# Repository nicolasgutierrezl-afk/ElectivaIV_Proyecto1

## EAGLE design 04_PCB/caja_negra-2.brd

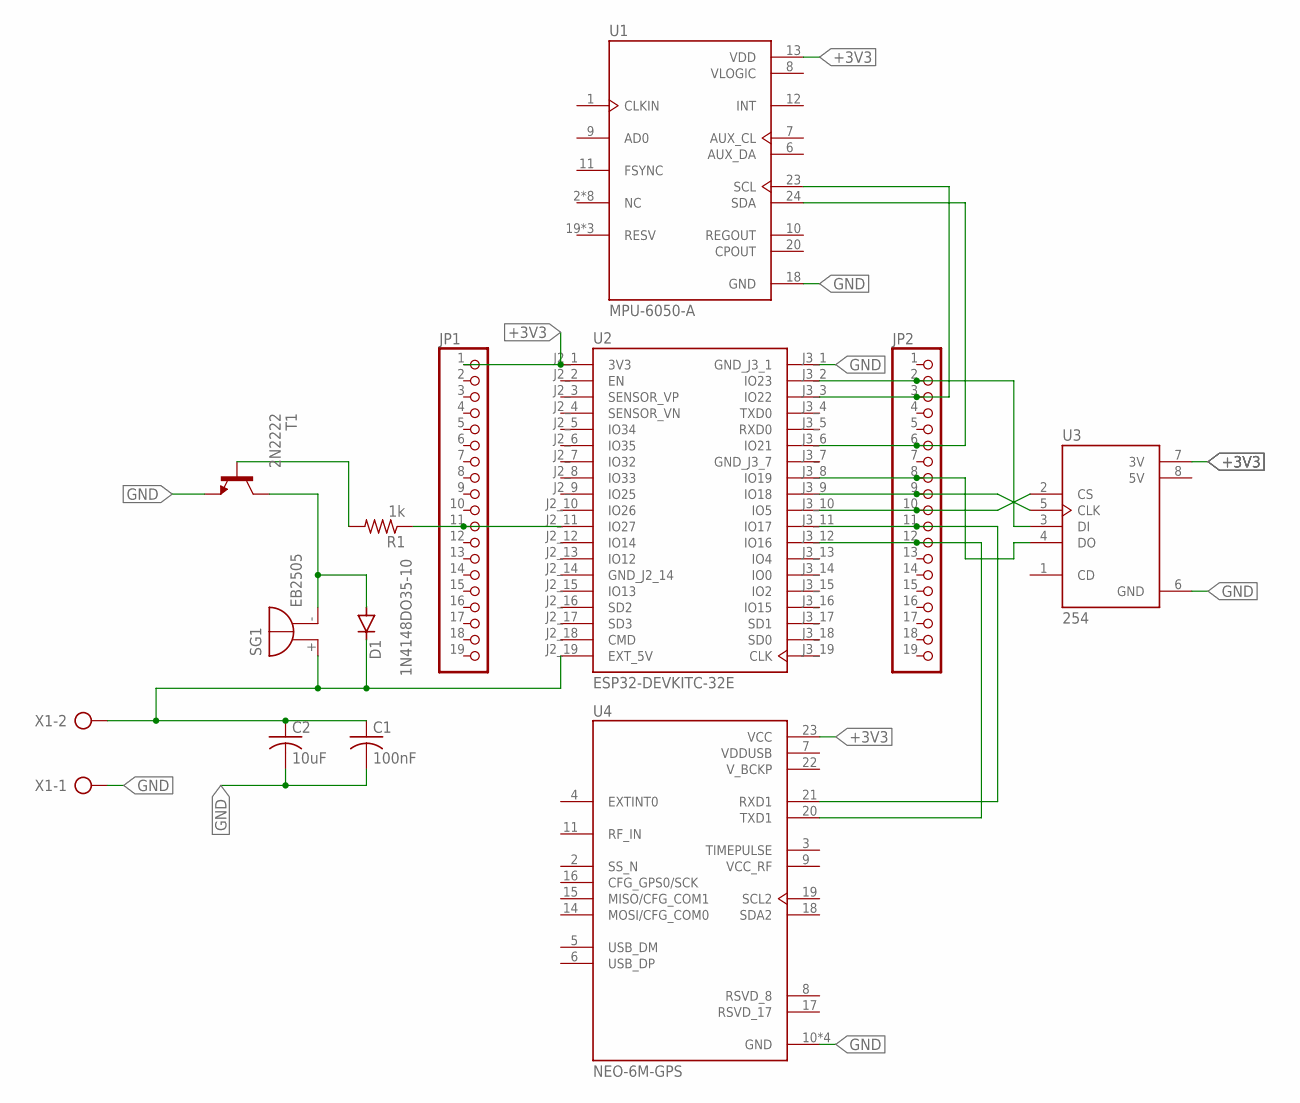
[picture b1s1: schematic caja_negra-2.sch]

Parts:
C1: 100nF; C025-024X044
C2: 10uF; C025-024X044
D1: 1N4148DO35-10; DO35-10
JP1, JP2: PINHD-1X19; 1X19
R1: 1k; 0204V
SG1: EB2505
T1: 2N2222; TO18
U1: MPU-6050-A; QFN50P400X400X95-24N
U2: ESP32-DEVKITC-32E; MODULE_ESP32-DEVKITC-32E
U3: 254; MODULE_254
U4: NEO-6M-GPS; XCVR_NEO-6M-GPS
X1: AK500/2-H

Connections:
5V: U3.8 (5V)
+3V3: JP1.1, U1.13 (VDD), U2.J2_1 (3V3), U3.7 (3V), U4.23 (VCC)
GND: C1.2, C2.2, T1.1 (E), U1.18 (GND), U2.J3_1 (GND_J3_1), U3.6 (GND), U4.10 (GND), U4.12 (GND), U4.13 (GND), U4.24 (GND), X1.1
GND_J2_14: U2.J2_14 (GND_J2_14)
GND_J3_7: U2.J3_7 (GND_J3_7)
unnamed: JP2.6, U1.24 (SDA), U2.J3_6 (IO21)
unnamed: JP2.3, U1.23 (SCL), U2.J3_3 (IO22)
unnamed: JP2.12, U2.J3_12 (IO16), U4.20 (TXD1)
unnamed: JP2.11, U2.J3_11 (IO17), U4.21 (RXD1)
unnamed: JP2.2, U2.J3_2 (IO23), U3.3 (DI)
unnamed: JP2.10, U2.J3_10 (IO5), U3.2 (CS)
unnamed: JP2.9, U2.J3_9 (IO18), U3.5 (CLK)
unnamed: JP2.8, U2.J3_8 (IO19), U3.4 (DO)
unnamed: JP1.11, R1.1, U2.J2_11 (IO27)
unnamed: C1.1, C2.1, D1.C, SG1.+, U2.J2_19 (EXT_5V), X1.2
unnamed: D1.A, SG1.-, T1.3 (C)
unnamed: R1.2, T1.2 (B)
VDDUSB: U4.7 (VDDUSB)
VLOGIC: U1.8 (VLOGIC)
V_BCKP: U4.22 (V_BCKP)

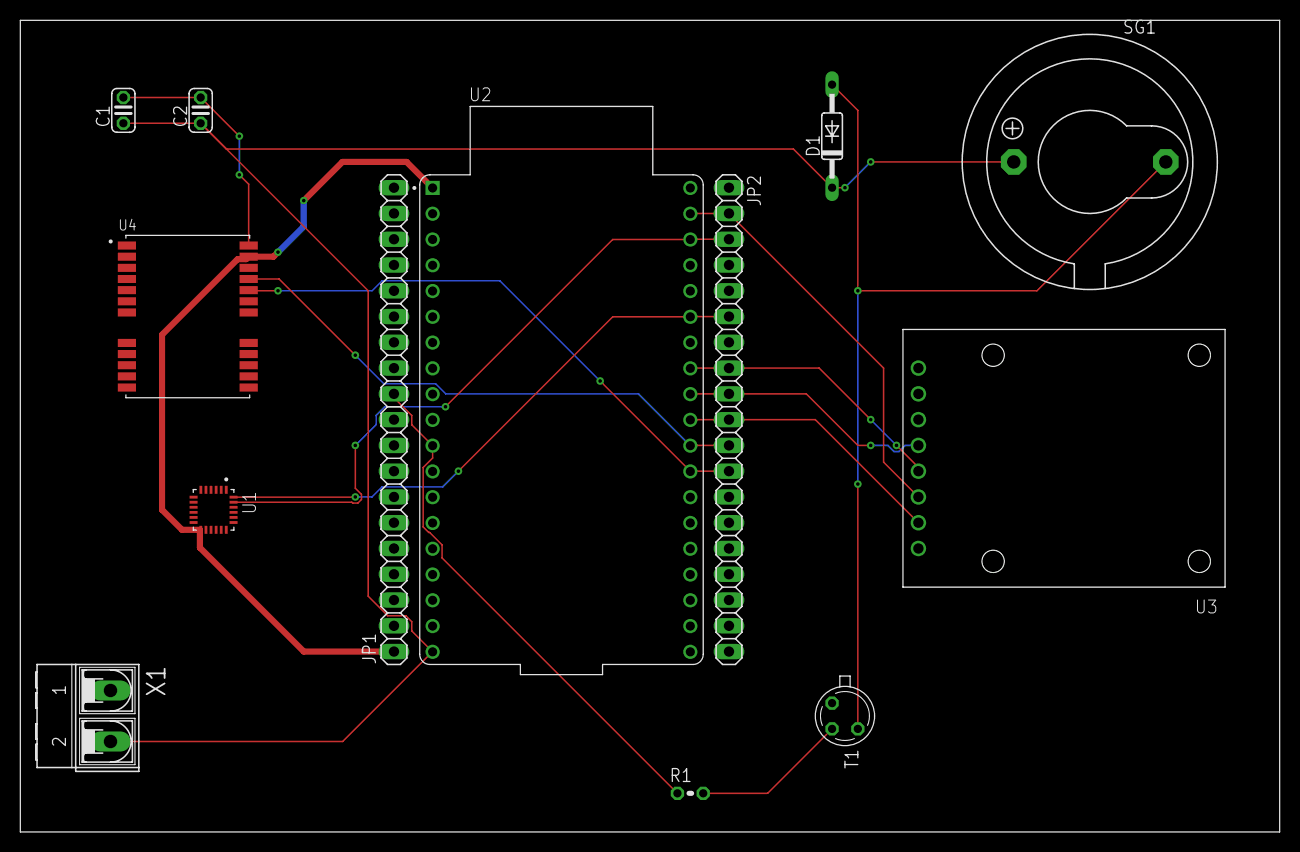
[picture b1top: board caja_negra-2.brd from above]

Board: 2 copper layers, 124.1 x 80.0 mm, 13 parts (0 on the bottom side), 14 nets.

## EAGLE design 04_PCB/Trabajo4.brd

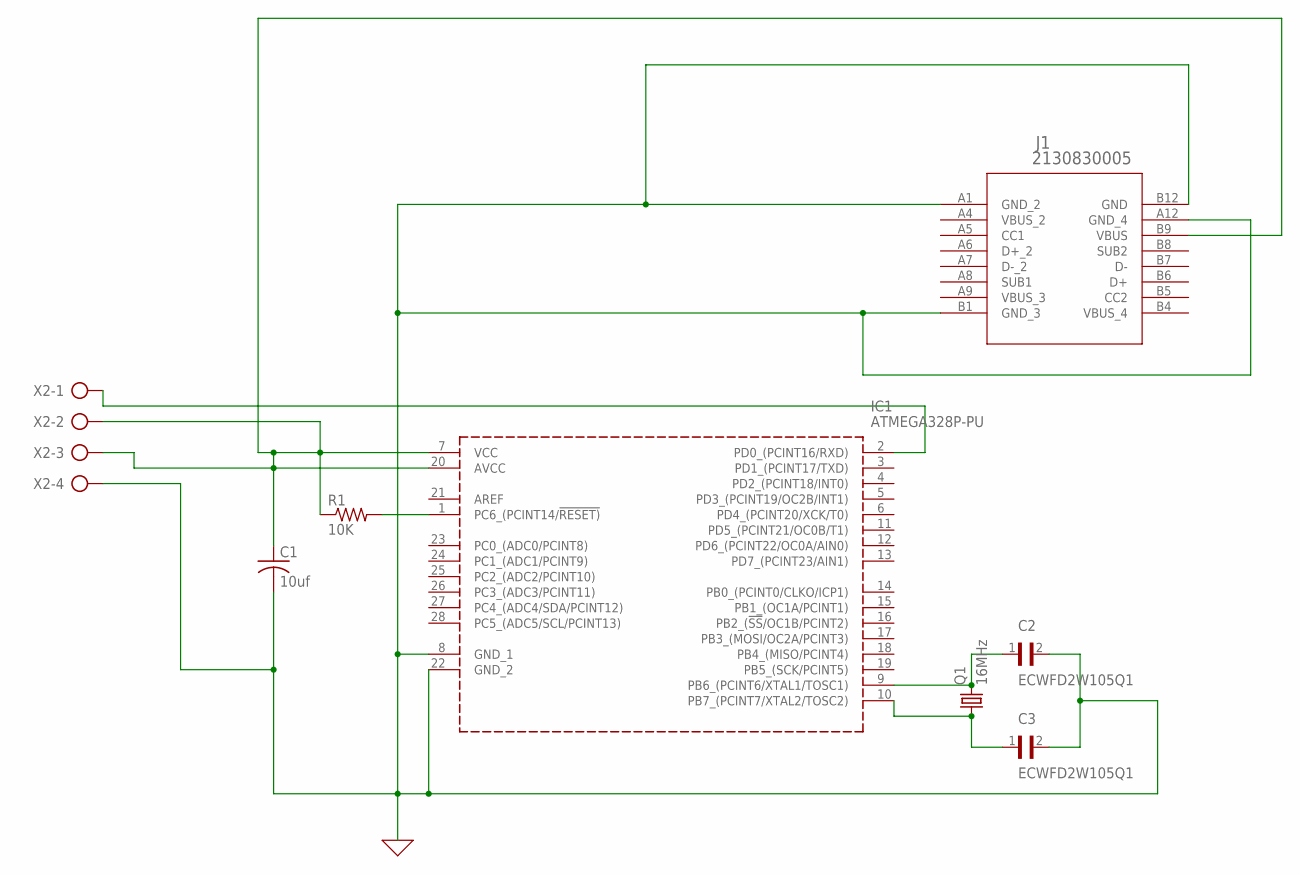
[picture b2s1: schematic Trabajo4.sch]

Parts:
C1: 10uf; C025-024X044
C2, C3: ECWFD2W105Q1; CAPRR1000W60L1260T920H1390
IC1: ATMEGA328P-PU; DIP794W53P254L3467H457Q28N
J1: 2130830005; 2130830005_MOL
Q1: 16MHz; HC33U-V
R1: 10K; 0204V
X2: AK500/4-H

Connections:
0: C1.2, C2.2, C3.2, IC1.8 (GND_1), IC1.22 (GND_2), J1.A1 (GND_2), J1.A12 (GND_4), J1.B1 (GND_3), J1.B12 (GND), X2.4
unnamed: C2.1, IC1.9 (PB6_(PCINT6/XTAL1/TOSC1)), Q1.2
unnamed: C3.1, IC1.10 (PB7_(PCINT7/XTAL2/TOSC2)), Q1.1
unnamed: IC1.2 (PD0_(PCINT16/RXD)), X2.1
unnamed: IC1.1 (PC6_(PCINT14/!RESET)), R1.2
unnamed: C1.1, IC1.7 (VCC), IC1.20 (AVCC), J1.B9 (VBUS), R1.1, X2.2, X2.3
VBUS_2: J1.A4 (VBUS_2)
VBUS_3: J1.A9 (VBUS_3)
VBUS_4: J1.B4 (VBUS_4)

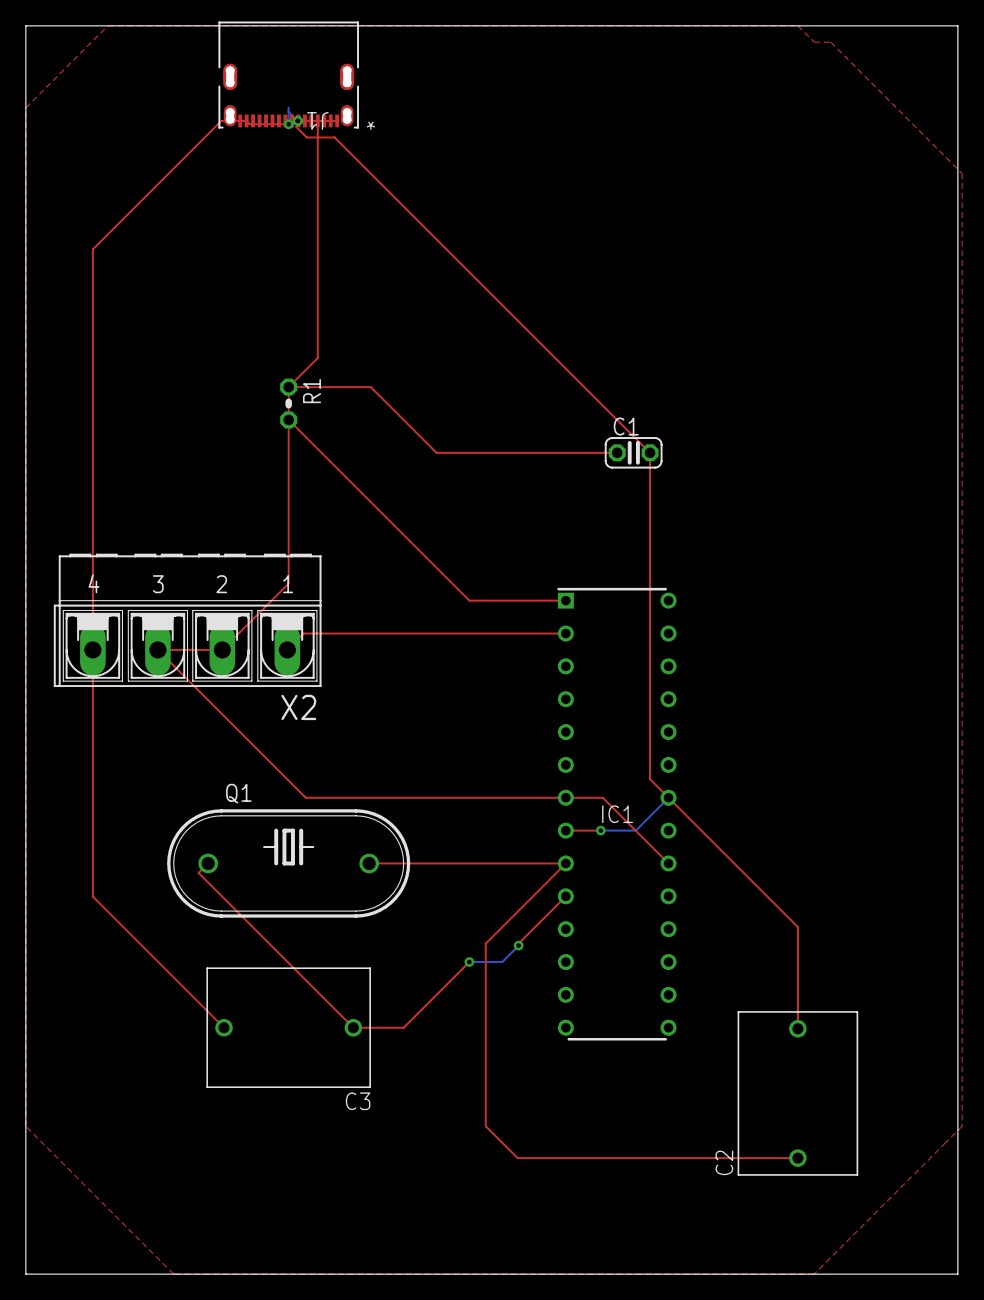
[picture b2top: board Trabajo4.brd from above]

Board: 2 copper layers, 72.1 x 96.5 mm, 8 parts (0 on the bottom side), 6 nets.

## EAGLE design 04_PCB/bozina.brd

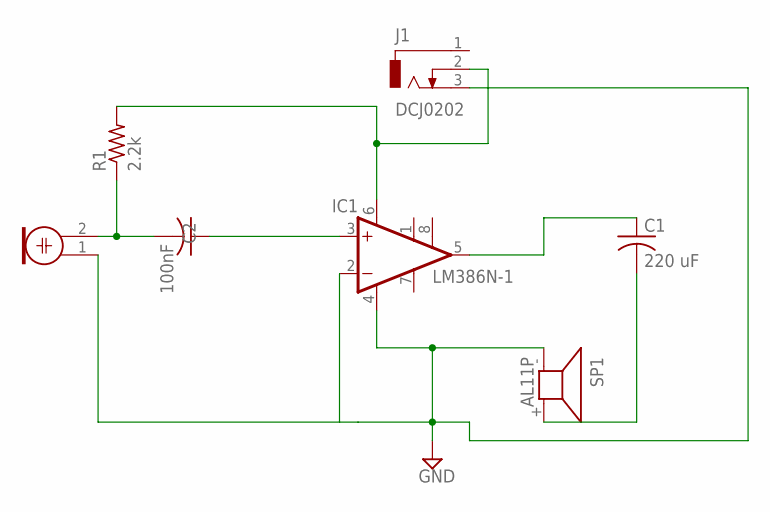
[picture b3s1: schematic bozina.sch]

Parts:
C1: 220 uF; C025-024X044
C2: 100nF; C025-024X044
IC1: LM386N-1; DIL08
J1: DCJ0202
M1: ELECTRET_MICROPHON-F6050AP; F6050AP
R1: 2.2k; 0204/5
SP1: AL11P

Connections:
GND: IC1.2 (-IN), IC1.4 (GND), J1.3, M1.1, SP1.- (1)
unnamed: IC1.6 (VS), J1.2, R1.2
unnamed: C1.2, SP1.+ (2)
unnamed: C1.1, IC1.5 (OUT)
unnamed: C2.2, M1.2, R1.1
unnamed: C2.1, IC1.3 (+IN)

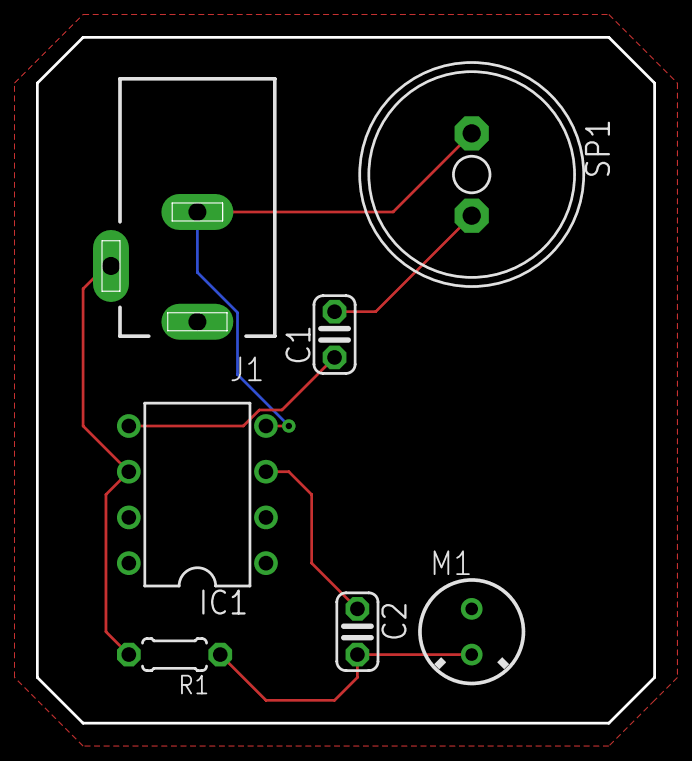
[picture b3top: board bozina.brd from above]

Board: 2 copper layers, 34.3 x 38.1 mm, 7 parts (0 on the bottom side), 6 nets.
